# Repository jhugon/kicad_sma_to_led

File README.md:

# SMA to LED Board

This KiCad board lets you hook a signal generator up to an LED.

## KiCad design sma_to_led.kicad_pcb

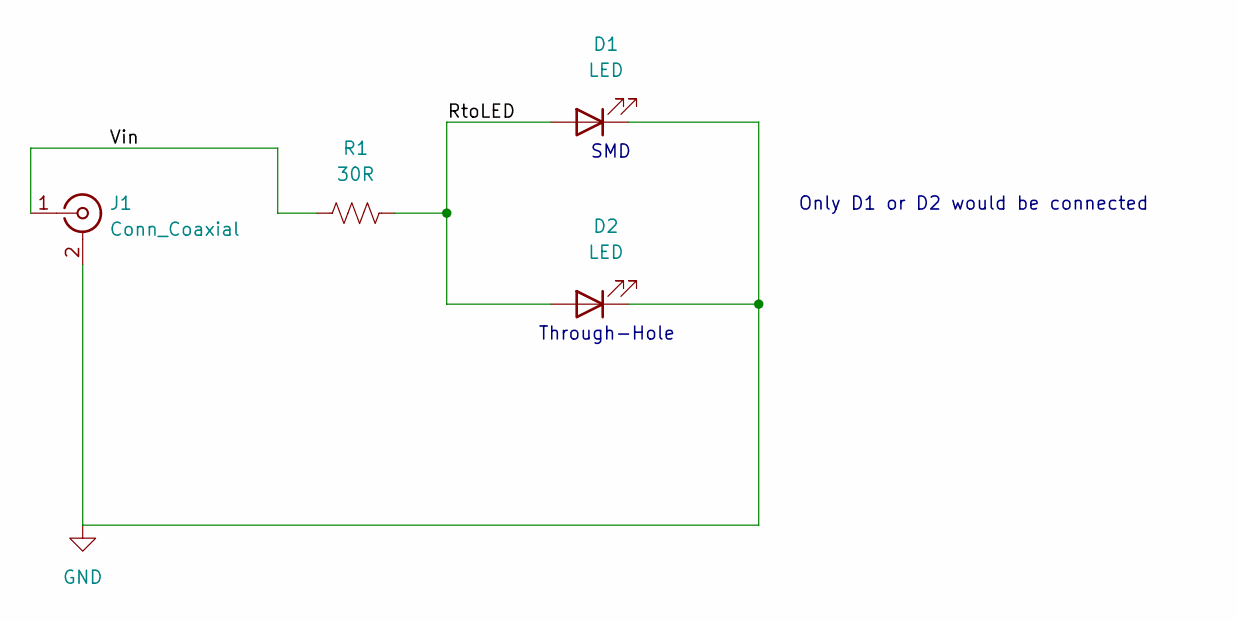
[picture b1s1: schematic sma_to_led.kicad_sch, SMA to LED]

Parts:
D1: LED; LED_1206_3216Metric_Pad1.42x1.75mm_HandSolder; Part LTST-C150TBKT
D2: LED; LED_D5.0mm; Part C503B-BAS-CX0B0462
J1: Conn_Coaxial; SMA_Amphenol_132289_EdgeMount; Part 132289
R1: 30R; R_1206_3216Metric_Pad1.30x1.75mm_HandSolder; Part CRCW120627R0FKEAC

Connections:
/RtoLED: D1.2 (A), D2.2 (A), R1.2
/Vin: J1.1 (In), R1.1
GND: D1.1 (K), D2.1 (K), J1.2 (Ext)

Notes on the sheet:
SMD
Only D1 or D2 would be connected
Through-Hole

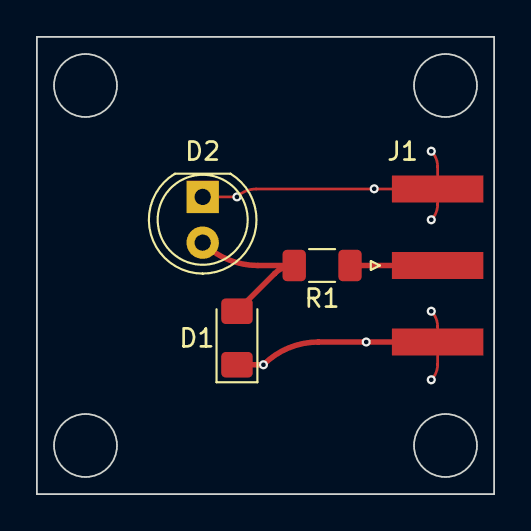
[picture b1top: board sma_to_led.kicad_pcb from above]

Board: 2 copper layers, 25.4 x 25.4 mm, 4 parts (0 on the bottom side), 3 nets.
